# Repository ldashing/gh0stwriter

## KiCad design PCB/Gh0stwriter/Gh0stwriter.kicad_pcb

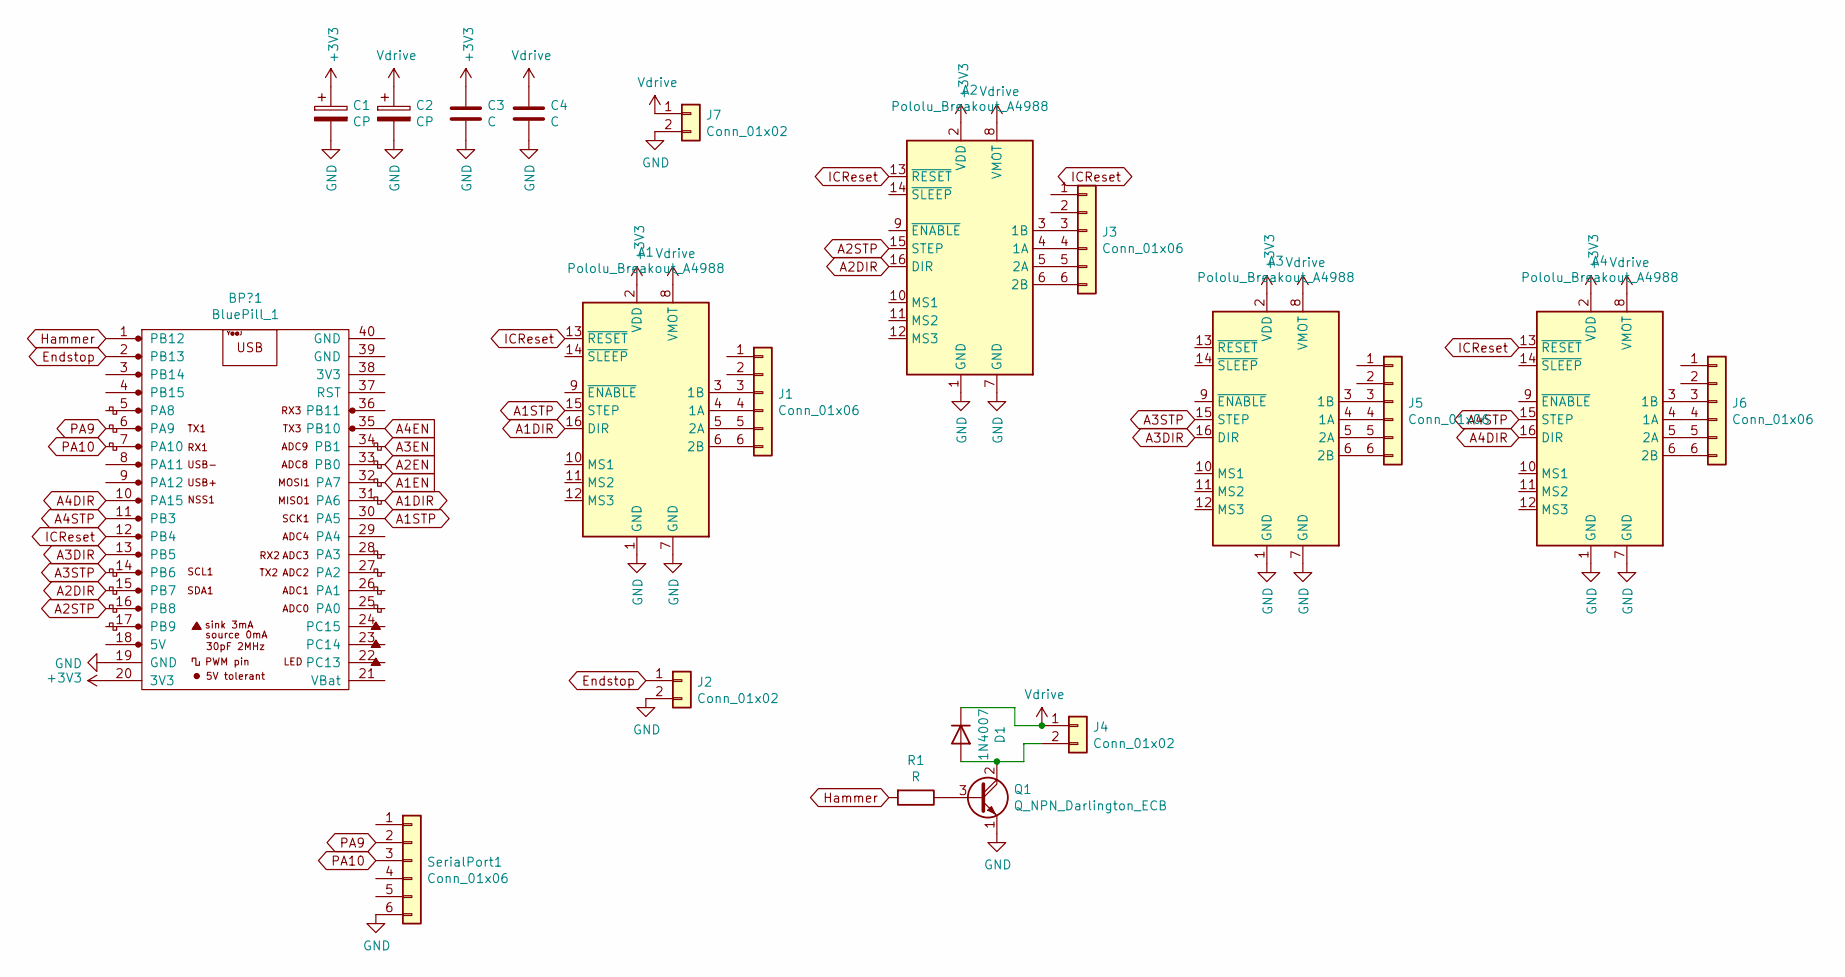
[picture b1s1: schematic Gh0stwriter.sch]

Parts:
A1, A2, A3, A4: Pololu_Breakout_A4988; Pololu_Breakout-16_15.2x20.3mm
BP?1: BluePill_1; YAAJ_BluePill
C1, C2: CP; CP_Radial_D6.3mm_P2.50mm
C3, C4: C; C_Disc_D4.7mm_W2.5mm_P5.00mm
D1: 1N4007; D_DO-35_SOD27_P2.54mm_Vertical_AnodeUp
J1, J3, J5, J6: Conn_01x06; JST_XH_B6B-XH-A_1x06_P2.50mm_Vertical
J2, J4: Conn_01x02; JST_XH_B2B-XH-A_1x02_P2.50mm_Vertical
J7: Conn_01x02; TerminalBlock_Phoenix_MKDS-1,5-2_1x02_P5.00mm_Horizontal
Q1: Q_NPN_Darlington_ECB; TO-126-3_Vertical
R1: R; R_Axial_DIN0207_L6.3mm_D2.5mm_P10.16mm_Horizontal
SerialPort1: Conn_01x06; PinHeader_1x06_P2.54mm_Vertical

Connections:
+3V3: A1.2 (VDD), A2.2 (VDD), A3.2 (VDD), A4.2 (VDD), BP?1.20 (3V3), C1.1, C3.1
A1DIR: A1.16 (DIR), BP?1.31 (PA6)
A1STP: A1.15 (STEP), BP?1.30 (PA5)
A2DIR: A2.16 (DIR), BP?1.15 (PB7)
A2STP: A2.15 (STEP), BP?1.16 (PB8)
A3DIR: A3.16 (DIR), BP?1.13 (PB5)
A3STP: A3.15 (STEP), BP?1.14 (PB6)
A4DIR: A4.16 (DIR), BP?1.10 (PA15)
A4STP: A4.15 (STEP), BP?1.11 (PB3)
Endstop: BP?1.2 (PB13), J2.1
GND: A1.1 (GND), A1.7 (GND), A2.1 (GND), A2.7 (GND), A3.1 (GND), A3.7 (GND), A4.1 (GND), A4.7 (GND), BP?1.19 (GND), C1.2, C2.2, C3.2, C4.2, J2.2, J7.2, Q1.1 (E), SerialPort1.6
Hammer: BP?1.1 (PB12), R1.2
ICReset: A1.13 (~RESET), A2.13 (~RESET), A4.13 (~RESET), BP?1.12 (PB4)
unnamed: A1.3 (1B), J1.3
unnamed: A1.4 (1A), J1.4
unnamed: A1.5 (2A), J1.5
unnamed: A1.6 (2B), J1.6
unnamed: A2.3 (1B), J3.3
unnamed: A2.4 (1A), J3.4
unnamed: A2.5 (2A), J3.5
unnamed: A2.6 (2B), J3.6
unnamed: A3.3 (1B), J5.3
unnamed: A3.4 (1A), J5.4
unnamed: A3.5 (2A), J5.5
unnamed: A3.6 (2B), J5.6
unnamed: A4.3 (1B), J6.3
unnamed: A4.4 (1A), J6.4
unnamed: A4.5 (2A), J6.5
unnamed: A4.6 (2B), J6.6
unnamed: D1.2 (A), J4.2, Q1.2 (C)
unnamed: Q1.3 (B), R1.1
PA9: BP?1.6 (PA9), SerialPort1.2
PA10: BP?1.7 (PA10), SerialPort1.3
Vdrive: A1.8 (VMOT), A2.8 (VMOT), A3.8 (VMOT), A4.8 (VMOT), C2.1, C4.1, D1.1 (K), J4.1, J7.1

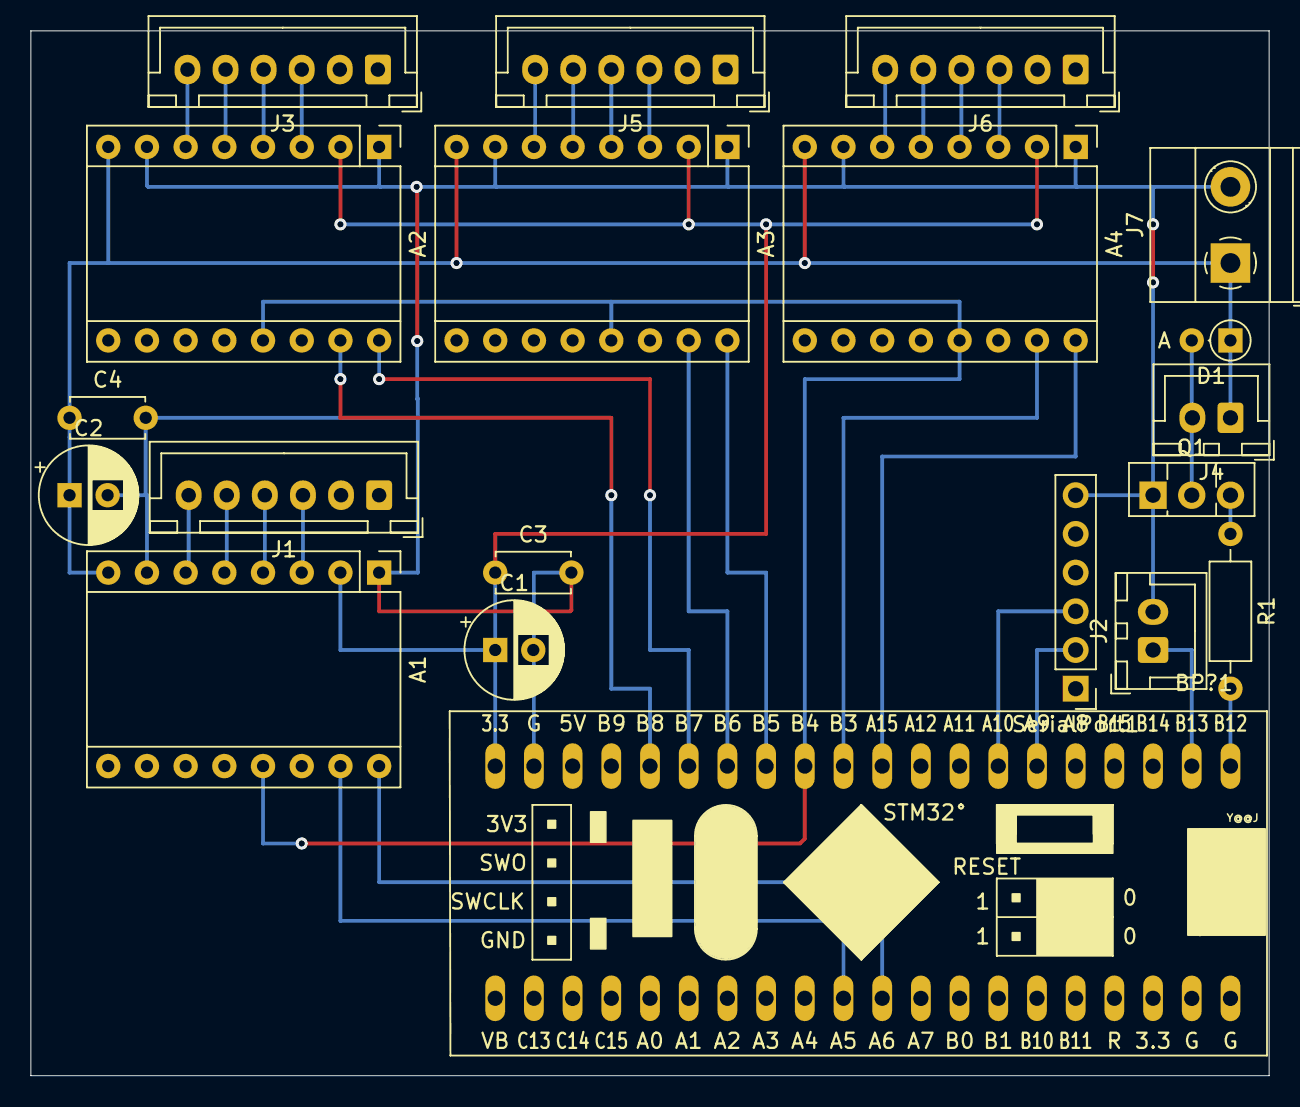
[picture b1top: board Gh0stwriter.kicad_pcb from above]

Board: 2 copper layers, 81.3 x 68.6 mm, 20 parts (0 on the bottom side), 34 nets.

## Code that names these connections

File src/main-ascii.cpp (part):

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BasicStepperDriver dial(MOTOR_STEPS, 6, 5, 4);
BasicStepperDriver head(MOTOR_STEPS, 12, 11, 10);
 */
BasicStepperDriver feed (MOTOR_STEPS, PA6, PA5, PA7);
BasicStepperDriver tape (MOTOR_STEPS, PB7, PB8, PB0);
BasicStepperDriver dial (MOTOR_STEPS, PA15, PB3, PB10);
BasicStepperDriver head (MOTOR_STEPS, PB5, PB6, PB1);

//some configuration:
int lineSpace = 40;		//Feed steps per new line
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	do {
		tape.move(1);
		delay(2);
	} while(digitalRead (PB13) == LOW);
	 do {
		 tape.move(1);
		 delay(2);
		} while(digitalRead (PB13) == HIGH);
		do {
			tape.move(1);
			delay(2);
		} while(digitalRead (PB13) == LOW);

	while (digitalRead (PB13) == HIGH)
{
	head.move (-1);
	delay (2);
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			while (Serial.available () == 0) {
			}

			digitalWrite (PB4, HIGH);
			delay (1);
			digitalWrite (PB4, LOW);
			delay (1);
			digitalWrite (PB4, HIGH);

			dialReset ();
			tape.move(-20);
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	void
hammerHit ()
{
	digitalWrite (PB12, HIGH);
	delay (10);
	digitalWrite (PB12, LOW);
	delay (10);
}

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	dial.disable ();
	head.disable ();

	pinMode (PB13, INPUT_PULLUP);
	pinMode (PB12, OUTPUT);
	digitalWrite (PB12, LOW);
	pinMode (PB12, OUTPUT);

	digitalWrite (PB4, HIGH);
	delay (1);
	digitalWrite (PB4, LOW);
	delay (1);
	digitalWrite (PB4, HIGH);

	dialReset ();

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
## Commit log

2020-05-27 Started the PCB
2020-05-27 Created pcb outline
2020-05-27 Started routing
2020-05-27 Most of pcb finished
2020-05-27 Fixed clipping of parts
2020-05-27 Removed unnasasary files
2020-05-28 Finished first Version of the pcb
2020-06-02 Serial comunication added
2020-06-02 Make modifications
2020-06-02 Fix issues
2020-06-02 Tada
2020-06-02 add ascii mapping file
2020-06-04 Added a timeout
2020-06-09 Start using ascii lut
2020-06-09 Refactor
    - Convert tabs to four spaces
    - correct indentation
    - move some functions to own files (functionallity wise)
2020-06-19 Add keyboard scanning
2020-06-19 remove some files
2020-07-28 Finish code polishing (may need bugfixes)
2020-07-28 Turn dial in the shorter direction
2020-08-11 Change the printing routine
